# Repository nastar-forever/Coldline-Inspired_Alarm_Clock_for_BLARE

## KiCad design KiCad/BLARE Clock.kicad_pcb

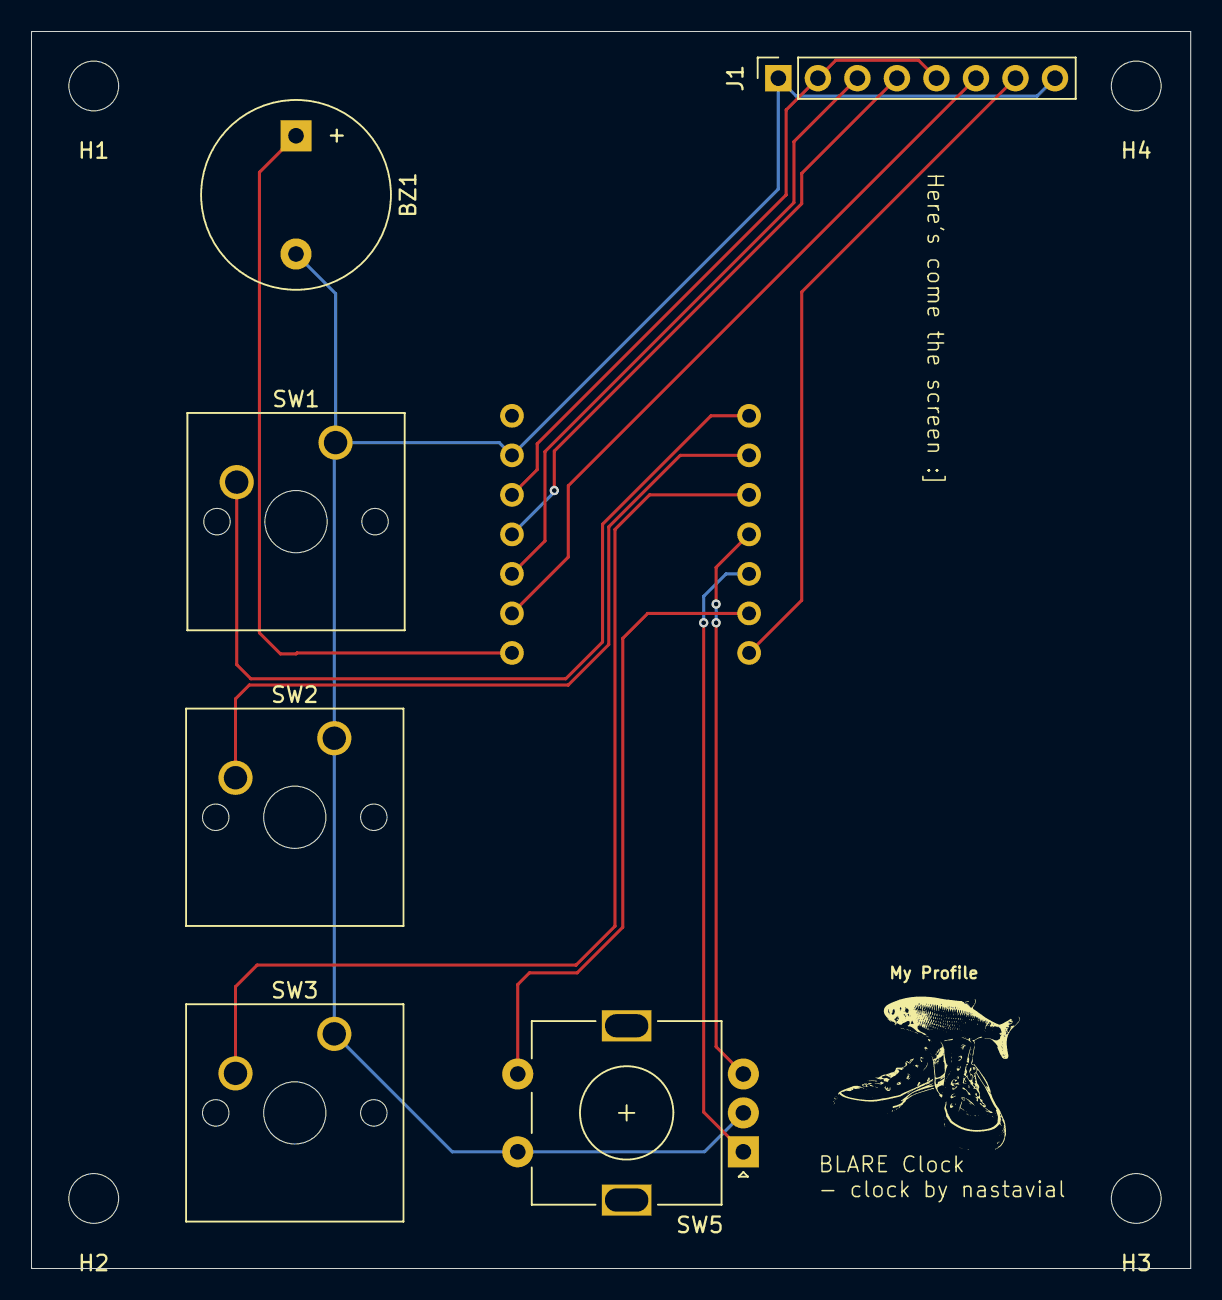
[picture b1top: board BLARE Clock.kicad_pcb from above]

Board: 2 copper layers, 74.5 x 79.5 mm, 12 parts (1 on the bottom side), 13 nets.

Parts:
BZ1: Buzzer; Buzzer_12x9.5RM7.6
H1, H2, H3, H4: MountingHole; MountingHole_3.2mm_M3
J1: Conn_01x08_Pin; PinSocket_1x08_P2.54mm_Vertical
My Profile: LOGO; NastavialPfP
SW1, SW2, SW3: SW_Push; SW_Cherry_MX_1.00u_PCB
SW5: RotaryEncoder_Switch; RotaryEncoder_Alps_EC11E-Switch_Vertical_H20mm
U1: XIAO-ESP32-C3-SMD; XIAO-ESP32-C3-DIP

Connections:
+3.3V: J1.2, J1.5, U1.12 (3V3_OUT)
/CS: J1.7, U1.7 (D6)
/DC: J1.6, U1.9 (D8)
/RE Click: SW5.S1, U1.6 (D5)
/SCL: J1.3, U1.10 (D9/BOOT)
/SDA: J1.4, U1.11 (D10)
GND: BZ1.2 (-), J1.1, J1.8, SW1.1, SW2.1, SW3.1, SW5.C, SW5.S2, U1.13 (GND)
unnamed: BZ1.1 (+), U1.8 (D7)
unnamed: SW1.2, U1.1 (D0)
unnamed: SW2.2, U1.2 (D1)
unnamed: SW3.2, U1.3 (D2)
unnamed: SW5.B, U1.4 (D3)
unnamed: SW5.A, U1.5 (D4)
